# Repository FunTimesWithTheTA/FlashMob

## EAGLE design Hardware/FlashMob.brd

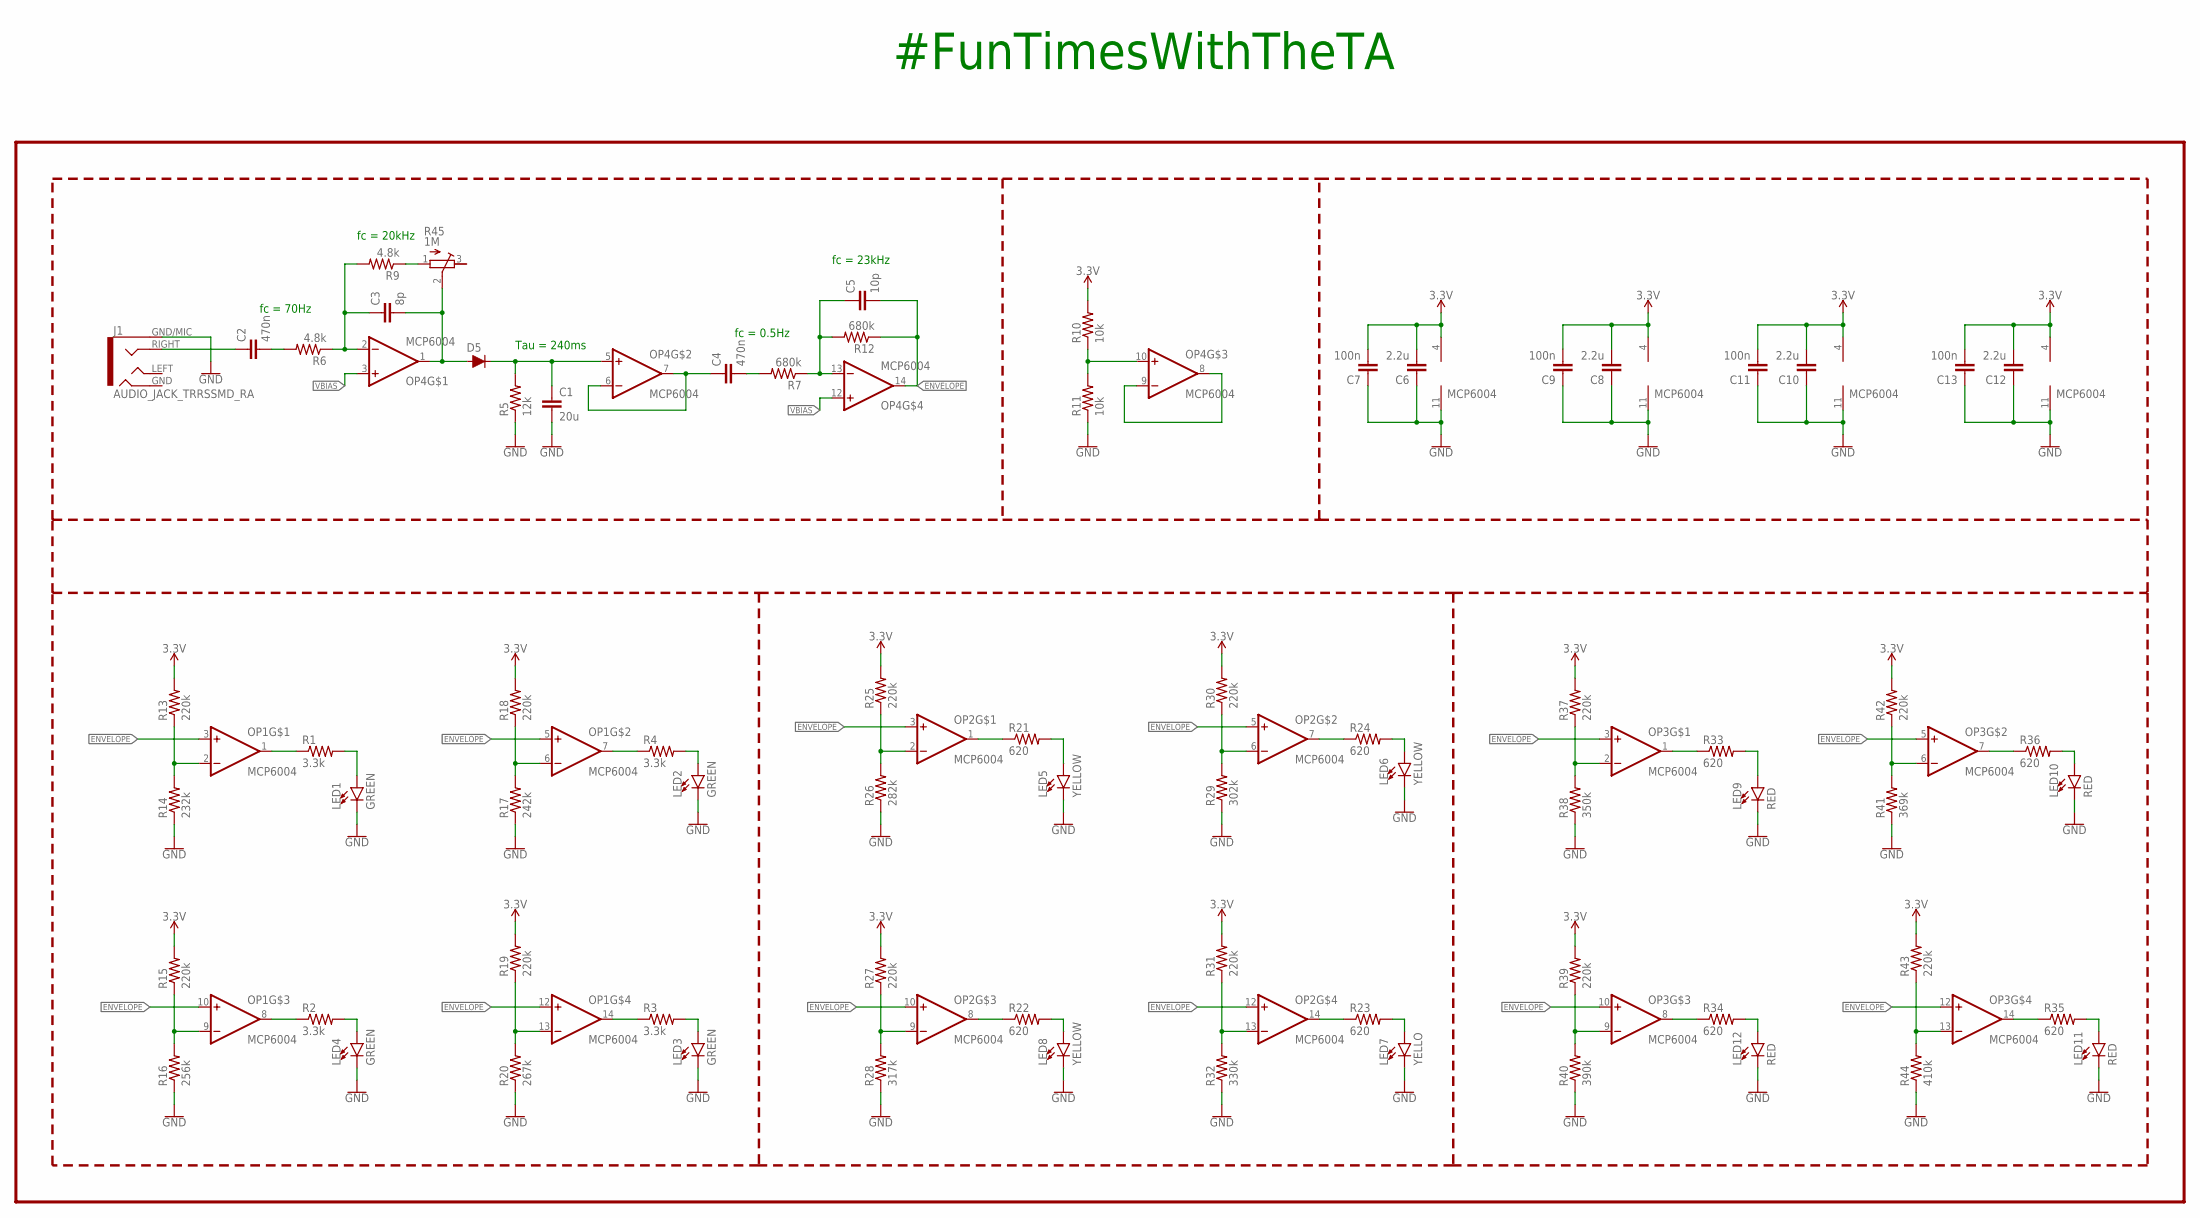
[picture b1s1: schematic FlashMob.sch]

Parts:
C1: 20u; C0402
C2, C4: 470n; C0402
C3: 8p; C0402
C5: 10p; C0402
C6, C8, C10, C12: 2.2u; C0402
C7, C9, C11, C13: 100n; C0402
D5: DIODE-BAS16J; SOD-323
J1: AUDIO_JACK_TRRSSMD_RA; AUDIO_JACK_3.5MM_TRRS_SMD_RA
LED1, LED2, LED3, LED4: GREEN; LED-0603
LED5, LED6, LED8: YELLOW; LED-0603
LED7: YELLO; LED-0603
LED9, LED10, LED11, LED12: RED; LED-0603
OP1, OP2, OP3, OP4: MCP6004; TSSOP14
R1, R2, R3, R4: 3.3k; R0402
R5: 12k; R0402
R6, R9: 4.8k; R0402
R7, R12: 680k; R0402
R10, R11: 10k; R0402
R13, R15, R18, R19, R25, R27, R30, R31, R37, R39, R42, R43: 220k; R0402
R14: 232k; R0402
R16: 256k; R0402
R17: 242k; R0402
R20: 267k; R0402
R21, R22, R23, R24, R33, R34, R35, R36: 620; R0402
R26: 282k; R0402
R28: 317k; R0402
R29: 302k; R0402
R32: 330k; R0402
R38: 350k; R0402
R40: 390k; R0402
R41: 369k; R0402
R44: 410k; R0402
R45: 1M; 16MMROTARYPOT
U$1: REVISION.A; REV.A

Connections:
3.3V: C6.2, C7.2, C8.2, C9.2, C10.2, C11.2, C12.2, C13.2, OP1.4 (V+), OP2.4 (V+), OP3.4 (V+), OP4.4 (V+), R10.2, R13.2, R15.2, R18.2, R19.2, R25.2, R27.2, R30.2, R31.2, R37.2, R39.2, R42.2, R43.2
ENVELOPE: C5.2, OP1.3 (+IN), OP1.5 (+IN), OP1.10 (+IN), OP1.12 (+IN), OP2.3 (+IN), OP2.5 (+IN), OP2.10 (+IN), OP2.12 (+IN), OP3.3 (+IN), OP3.5 (+IN), OP3.10 (+IN), OP3.12 (+IN), OP4.14 (OUT), R12.1
GND: C1.2, C6.1, C7.1, C8.1, C9.1, C10.1, C11.1, C12.1, C13.1, J1.GND/MIC (SLEEVE), LED1.C, LED2.C, LED3.C, LED4.C, LED5.C, LED6.C, LED7.C, LED8.C, LED9.C, LED10.C, LED11.C, LED12.C, OP1.11 (V-), OP2.11 (V-), OP3.11 (V-), OP4.11 (V-), R5.1, R11.1, R14.1, R16.1, R17.1, R20.1, R26.1, R28.1, R29.1, R32.1, R38.1, R40.1, R41.1, R44.1
unnamed: OP1.1 (OUT), R1.1
unnamed: OP1.8 (OUT), R2.1
unnamed: OP1.14 (OUT), R3.1
unnamed: OP1.7 (OUT), R4.1
unnamed: C2.2, R6.2
unnamed: C4.1, OP4.6 (-IN), OP4.7 (OUT)
unnamed: LED1.A, R1.2
unnamed: LED4.A, R2.2
unnamed: LED3.A, R3.2
unnamed: LED2.A, R4.2
unnamed: C3.1, OP4.2 (-IN), R6.1, R9.2
unnamed: R9.1, R45.1 (A)
unnamed: C5.1, OP4.13 (-IN), R7.1, R12.2
unnamed: C3.2, D5.A, OP4.1 (OUT), R45.2 (S)
unnamed: OP4.10 (+IN), R10.1, R11.2
unnamed: OP4.8 (OUT), OP4.9 (-IN)
unnamed: C4.2, R7.2
unnamed: C2.1, J1.RIGHT (RING1)
unnamed: C1.1, D5.C, OP4.5 (+IN), R5.2
unnamed: OP1.2 (-IN), R13.1, R14.2
unnamed: OP1.9 (-IN), R15.1, R16.2
unnamed: OP1.6 (-IN), R17.2, R18.1
unnamed: OP1.13 (-IN), R19.1, R20.2
unnamed: OP2.1 (OUT), R21.1
unnamed: OP2.8 (OUT), R22.1
unnamed: OP2.14 (OUT), R23.1
unnamed: OP2.7 (OUT), R24.1
unnamed: LED5.A, R21.2
unnamed: LED8.A, R22.2
unnamed: LED7.A, R23.2
unnamed: LED6.A, R24.2
unnamed: OP2.2 (-IN), R25.1, R26.2
unnamed: OP2.9 (-IN), R27.1, R28.2
unnamed: OP2.6 (-IN), R29.2, R30.1
unnamed: OP2.13 (-IN), R31.1, R32.2
unnamed: OP3.1 (OUT), R33.1
unnamed: OP3.8 (OUT), R34.1
unnamed: OP3.14 (OUT), R35.1
unnamed: OP3.7 (OUT), R36.1
unnamed: LED9.A, R33.2
unnamed: LED12.A, R34.2
unnamed: LED11.A, R35.2
unnamed: LED10.A, R36.2
unnamed: OP3.2 (-IN), R37.1, R38.2
unnamed: OP3.9 (-IN), R39.1, R40.2
unnamed: OP3.6 (-IN), R41.2, R42.1
unnamed: OP3.13 (-IN), R43.1, R44.2
VBIAS: OP4.3 (+IN), OP4.12 (+IN)

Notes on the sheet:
fc = 0.5Hz
fc = 23kHz
fc = 20kHz
fc = 70Hz
Tau = 240ms
#FunTimesWithTheTA

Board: 2 copper layers, 76 parts (0 on the bottom side), 51 nets, no tracks yet.

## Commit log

2018-06-21 updates from Fall 2017
2018-08-03 Made a few minor changes
2018-09-14 Adding the simulations for FlashMob
2018-10-24 Updating the document
2018-10-24 and we're live
2018-10-24 updates with testing procedure
